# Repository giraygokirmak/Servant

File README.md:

# Servant
ESP8266 PowerPlug 220volt Power Outlet remote control by Blynk/MQTT IoT Servers with it's own wifimanager/(Tasmota Firmware compatible)

For PCB go to https://www.oshpark.com/profiles/mgiraygokirmak

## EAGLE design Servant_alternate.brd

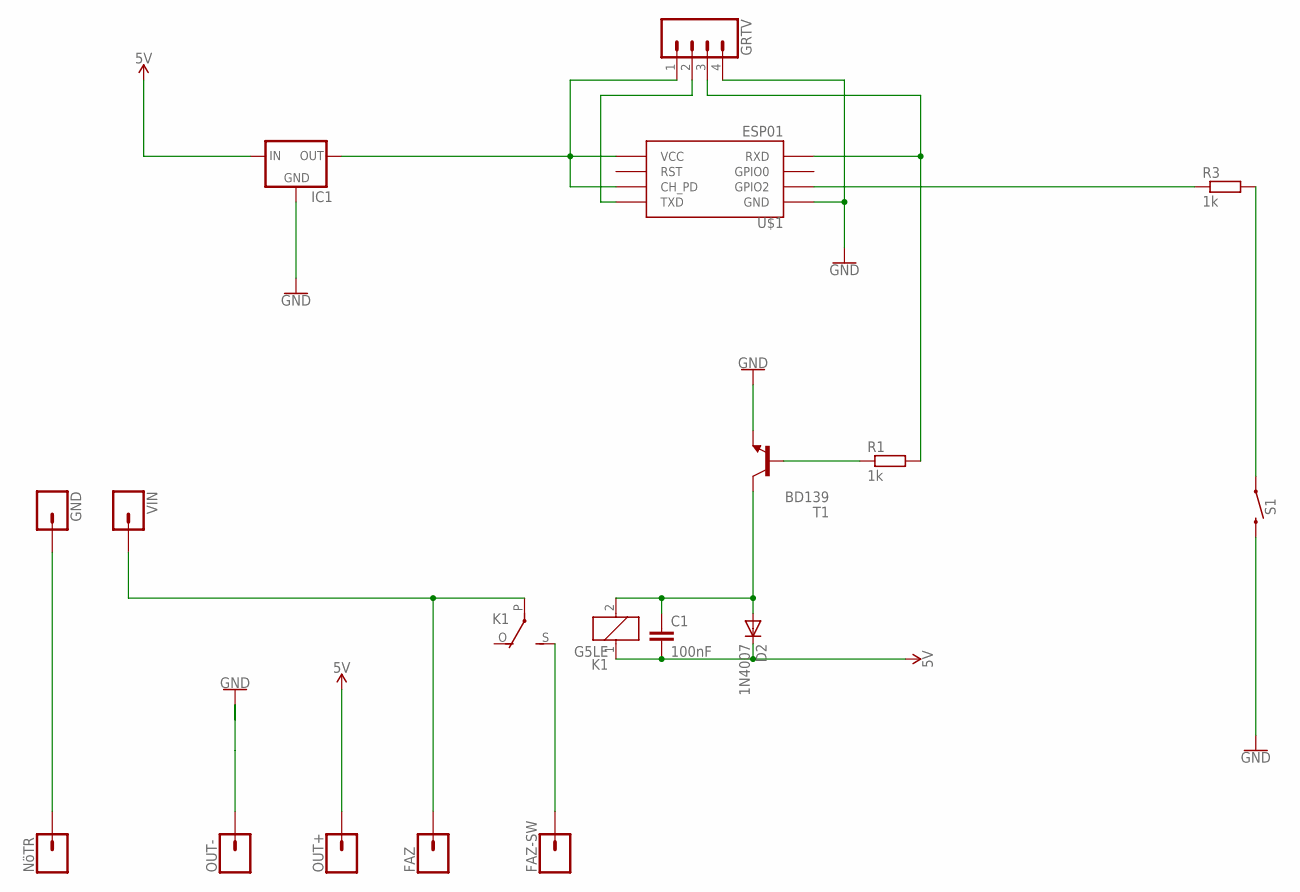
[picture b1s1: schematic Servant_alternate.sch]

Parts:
C1: 100nF; 1210
D2: 1N4007; SMB
FAZ: CONN_01PTH_LONGPAD; 1X01_LONGPAD
FAZ-SW: CONN_01PTH_LONGPAD; 1X01_LONGPAD
GND: CONN_01; 1X01
GRTV: CONN_041X04_NO_SILK; 1X04_NO_SILK
IC1: XC63FPM; SOT23
K1: G5LE
NöTR: CONN_01PTH_LONGPAD; 1X01_LONGPAD
OUT+: CONN_01; 1X01
OUT-: CONN_01; 1X01
R1, R3: 1k; R1206
S1: MOMENTARY-SWITCH-SPST-PTH-6.0MM; TACTILE_SWITCH_PTH_6.0MM
T1: BD139; TO126V
U$1: ESP01
VIN: CONN_01; 1X01

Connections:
5V: C1.2, D2.C, IC1.3 (IN), K1.1, OUT+.1
GND: GRTV.4, IC1.1 (GND), OUT-.1, S1.3 (2), T1.1 (E), U$1.GND
unnamed: GRTV.1, IC1.2 (OUT), U$1.CH_PD, U$1.VCC
unnamed: C1.1, D2.A, K1.2, T1.2 (C)
unnamed: R1.1, T1.3 (B)
unnamed: FAZ.1, K1.P, VIN.1
unnamed: FAZ-SW.1, K1.S
unnamed: GRTV.3, R1.2, U$1.RX (RXD)
unnamed: GRTV.2, U$1.TX (TXD)
unnamed: GND.1, NöTR.1
unnamed: R3.1, U$1.GPIO2
unnamed: R3.2, S1.1

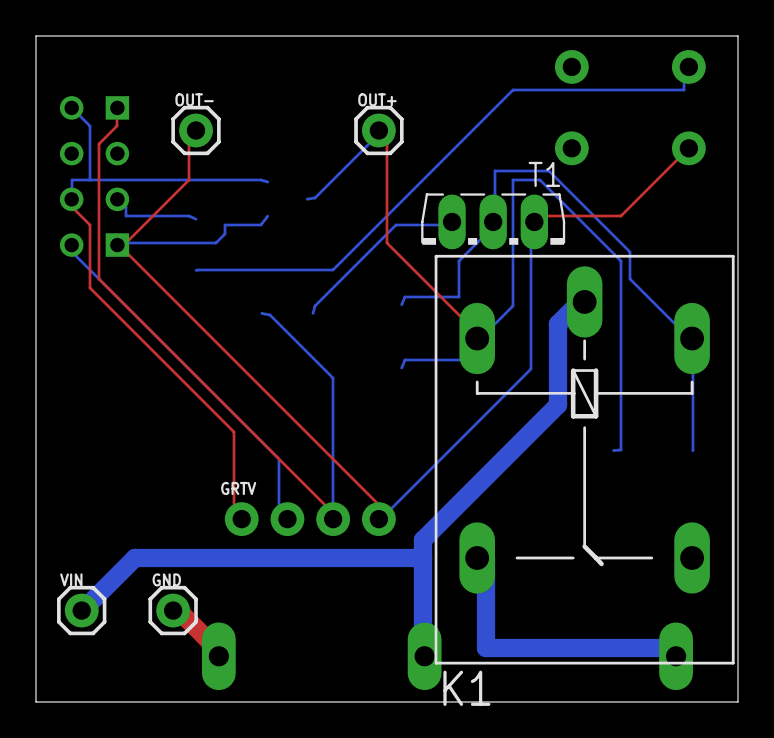
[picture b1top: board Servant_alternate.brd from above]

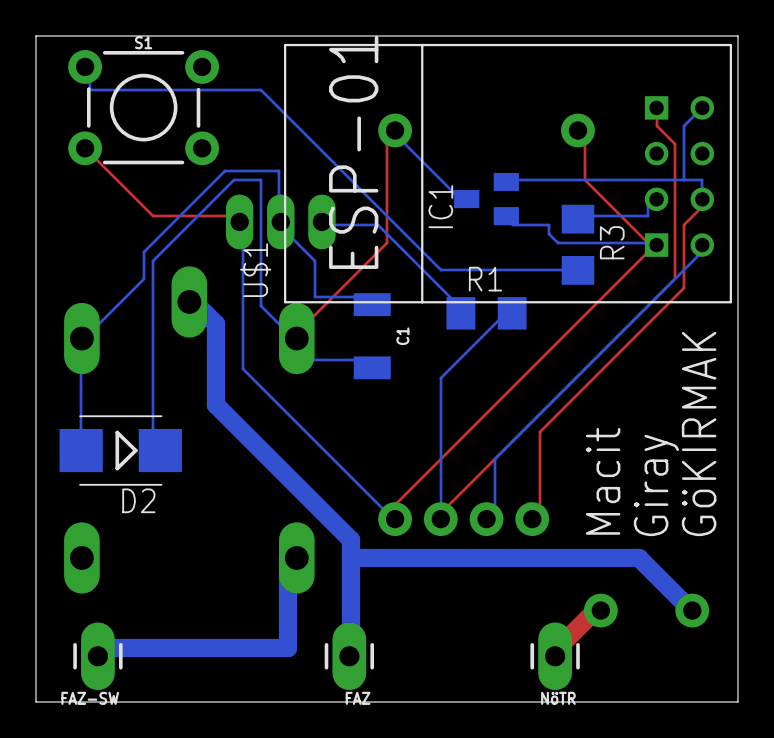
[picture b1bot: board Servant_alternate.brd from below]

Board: 2 copper layers, 39.0 x 37.0 mm, 17 parts (10 on the bottom side), 12 nets.

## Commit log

2017-09-28 Add files via upload
    Smaller version without status a led

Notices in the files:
parts and their libraries:
SparkFun-Capacitors: Licensing: Creative Commons ShareAlike 4.0 International - https://creativecommons.org/licenses/by-sa/4.0
